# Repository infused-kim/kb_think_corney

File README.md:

# ThinkCorney

A wireless corne / crkbd ergonomic keyboard clone with support for a trackpoint. Built with ergogen v4.

> **Warning**
>
> This keyboard is still under development and not ready for production use.
>
> You can find early stage code on the [develop branch](https://github.com/infused-kim/kb_think_corney/tree/develop) and gerbers in the [repo's releases section](https://github.com/infused-kim/kb_think_corney/releases).
,e
## Credits & Acknowledgements

- [Foostan's corne / crkbd](https://github.com/foostan/crkbd) for making the most popular ergo keyboard that is being used as the basis for this design
- Crehmann's [buzzard](https://github.com/crehmann/Buzzard) and [TPS42](https://github.com/crehmann/TPS42) for pioneering keyboards with trackpoints
- [Jon808517](https://reddit.com/r/ErgoMechKeyboards/comments/11ozztx/choc_spaced_corne_xiao/) for pointing me to the molex pico ezmate connector and joycon batteries
- And of course MrZealot for creating [ergogen](https://github.com/ergogen/ergogen)
- ceoloide for his awesome and creative ergogen tricks in [corney_island](https://github.com/ceoloide/corney-island/)

## License

**TLDR:**

- Personal use with attribution
- Commercial use not allowed

This work is licensed under a
[Creative Commons Attribution-ShareAlike 4.0 International License][cc-by-sa].

[![CC BY-SA 4.0][cc-by-sa-image]][cc-by-sa]

[cc-by-sa]: http://creativecommons.org/licenses/by-sa/4.0/
[cc-by-sa-image]: https://licensebuttons.net/l/by-sa/4.0/88x31.png
[cc-by-sa-shield]: https://img.shields.io/badge/License-CC%20BY--SA%204.0-lightgrey.svg

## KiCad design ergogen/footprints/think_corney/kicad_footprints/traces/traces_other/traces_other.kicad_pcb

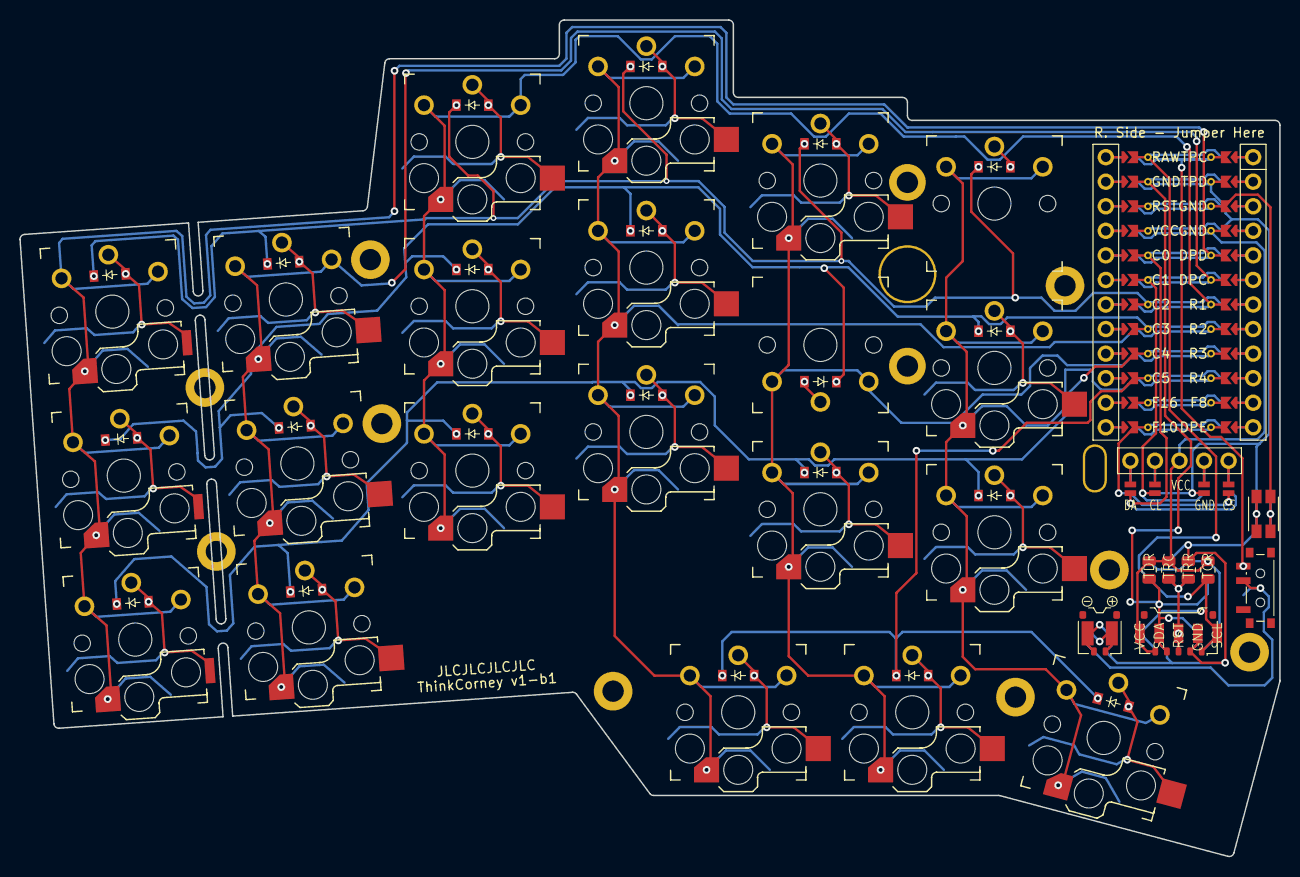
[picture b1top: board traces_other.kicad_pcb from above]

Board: 2 copper layers, 130.3 x 86.5 mm, 112 parts (0 on the bottom side), 46 nets.

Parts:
CONN1: conn_molex_pico_ezmate_1x02
CONN2: conn_molex_pico_ezmate_1x05
D1, D2, D3, D4, D5, D6, D7, D8, D9, D10, D11, D12, D13, D14, D15, D16, D17, D18, D19, D20, D21: ComboDiode
DISP1: nice!view
H1, H2, H3, H4, H5, H6, H7, H8, H9, H10: mounting_hole
ICON1: icon_bat
MCU1: nice_nano
P1", P2", P3", P4", P5", P6", P7", P8", P9", P10", P11", P12", P13", P14", P15", P16", P17", P18", P19", P20", P21", P22", P23", P24", P25", P26", P27", P28", P29", P30", P31", P32", P33", P34", P35", P36", P37", P38", P39", P40", P41", P42", P43", P44", P45", P46", P47", P48", P49": point_debugger
PAD1, PAD2: pads
S1, S2, S3, S4, S5, S6, S7, S8, S9, S10, S11, S12, S13, S14, S15, S16, S17, S18, S19, S20, S21: PG1350
SMD1: smd_805
SW1: power_switch
SW2: sw_reset_side
TP1: trackpoint_mount_t430

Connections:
BAT_P: CONN1.1, PAD1.1, PAD1.2, SW1.2, SW1.5
C0: MCU1.5, S12.1, S13.1, S14.1
C1: MCU1.6, S15.1, S16.1, S17.1
C2: MCU1.7, S1.1, S2.1, S3.1
C3: MCU1.8, S4.1, S5.1, S6.1, S9.1
C4: MCU1.9, S7.1, S10.1, S18.1, S19.1
C5: MCU1.10, S8.1, S11.1, S20.1, S21.1
DISP1_1: DISP1.1, DISP1.14, DISP1.27
DISP1_2: DISP1.2, DISP1.15, DISP1.26
DISP1_4: DISP1.4, DISP1.16, DISP1.25
DISP1_5: DISP1.5, DISP1.17, DISP1.24
DPC: DISP1.11, DISP1.21, MCU1.119
DPD: DISP1.10, DISP1.20, MCU1.120
DPE: DISP1.13, DISP1.23, MCU1.113
GND: CONN1.2, CONN2.2, DISP1.12, DISP1.22, MCU1.2, MCU1.121, MCU1.122, PAD1.1, PAD1.2, PAD2.2, PAD2.4, SMD1.3, SMD1.5, SW2.1
R1: D3.1, D6.1, D9.1, D12.1, D18.1, D20.1, MCU1.118
R2: D2.1, D5.1, D8.1, D11.1, D19.1, D21.1, MCU1.117
R3: D1.1, D4.1, D7.1, D10.1, D13.1, D14.1, MCU1.116
R4: D15.1, D16.1, D17.1, MCU1.115
RAW: MCU1.1, SW1.3, SW1.6
RST: MCU1.3, SW2.2
TPC: CONN2.1, MCU1.124, PAD2.1, PAD2.5, SMD1.2, SMD1.8
TPD: CONN2.4, MCU1.123, PAD2.2, PAD2.4, SMD1.2, SMD1.8
TPR: CONN2.3, PAD2.3, SMD1.4, SMD1.6
VCC: CONN2.5, DISP1.3, MCU1.4, PAD2.1, PAD2.5, SMD1.1, SMD1.3, SMD1.5, SMD1.7
home_cluster: D16.2, S10.2
index_bottom: D13.2, S7.2
index_home: D19.2, S19.2
index_top: D18.2, S18.2
inner_bottom: D14.2, S8.2
inner_cluster: D17.2, S11.2
inner_home: D21.2, S21.2
inner_top: D20.2, S20.2
middle_bottom: D10.2, S4.2
middle_home: D11.2, S5.2
middle_top: D12.2, S6.2
outer_bottom: D1.2, S12.2
outer_cluster: D15.2, S9.2
outer_home: D2.2, S13.2
outer_top: D3.2, S14.2
pinky_bottom: D4.2, S15.2
pinky_home: D5.2, S16.2
pinky_top: D6.2, S17.2
ring_bottom: D7.2, S1.2
ring_home: D8.2, S2.2
ring_top: D9.2, S3.2

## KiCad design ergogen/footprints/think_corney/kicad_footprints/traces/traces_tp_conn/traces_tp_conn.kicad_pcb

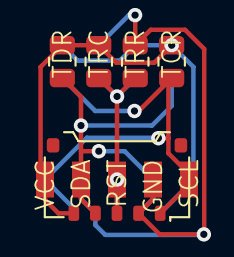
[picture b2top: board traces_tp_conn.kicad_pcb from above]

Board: 2 copper layers, 5 parts (0 on the bottom side), 5 nets.

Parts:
CONN2: conn_molex_pico_ezmate_1x05
P40", P41": point_debugger
PAD2: pads
SMD1: smd_805

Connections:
GND: CONN2.2, PAD2.2, PAD2.4, SMD1.3, SMD1.5
TPC: CONN2.1, PAD2.1, PAD2.5, SMD1.2, SMD1.8
TPD: CONN2.4, PAD2.2, PAD2.4, SMD1.2, SMD1.8
TPR: CONN2.3, PAD2.3, SMD1.4, SMD1.6
VCC: CONN2.5, PAD2.1, PAD2.5, SMD1.1, SMD1.3, SMD1.5, SMD1.7

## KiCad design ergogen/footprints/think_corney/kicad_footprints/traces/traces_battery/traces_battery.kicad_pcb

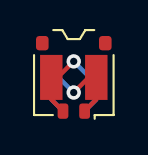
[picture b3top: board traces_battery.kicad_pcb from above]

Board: 2 copper layers, 4 parts (0 on the bottom side), 2 nets.

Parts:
CONN1: conn_molex_pico_ezmate_1x02
P35", P36": point_debugger
PAD1: pads

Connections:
BAT_P: CONN1.1, PAD1.1, PAD1.2
GND: CONN1.2, PAD1.1, PAD1.2

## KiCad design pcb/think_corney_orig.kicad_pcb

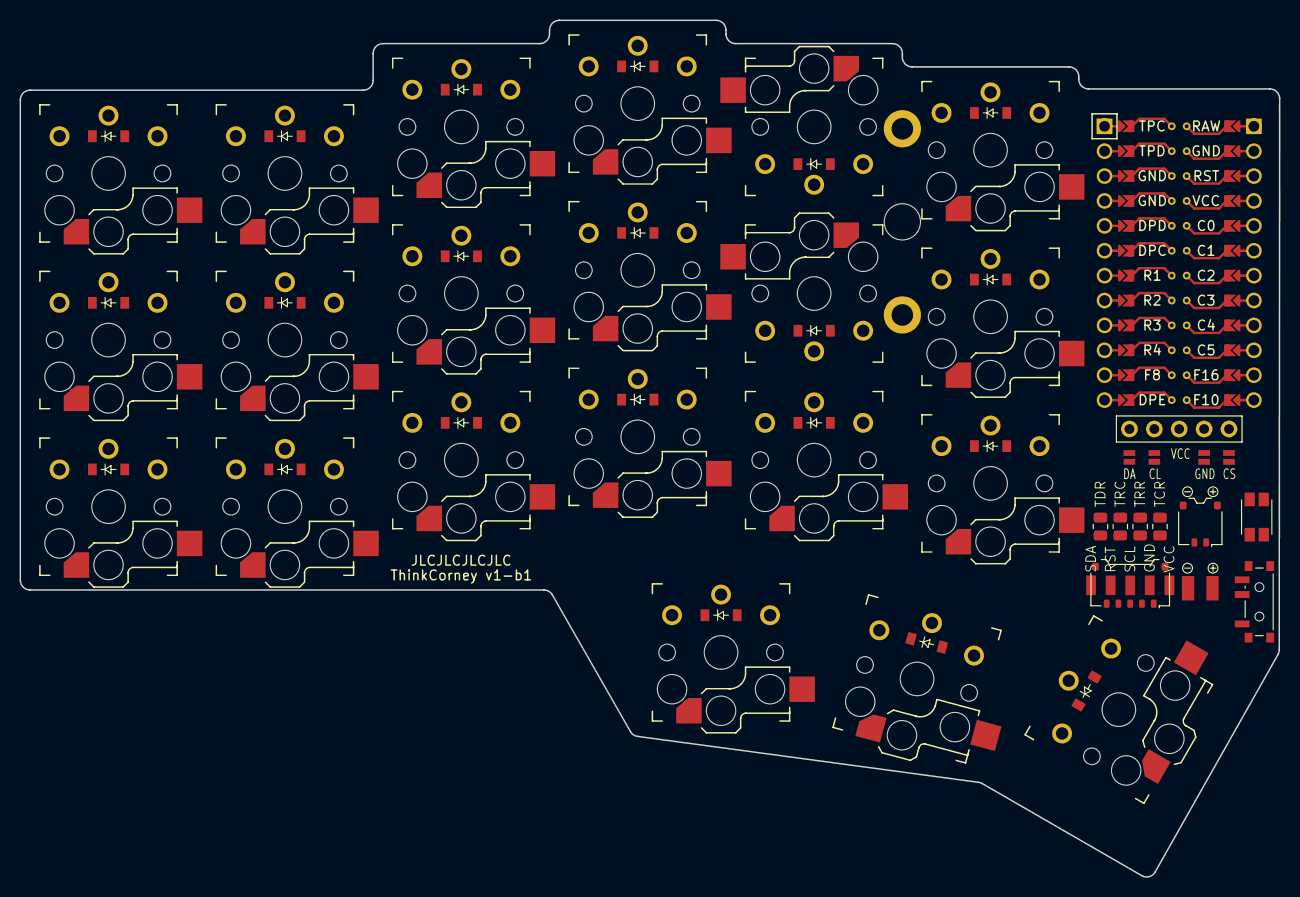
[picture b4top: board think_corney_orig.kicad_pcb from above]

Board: 2 copper layers, 128.5 x 87.4 mm, 54 parts (0 on the bottom side), 46 nets, no tracks yet.

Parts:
CONN1: conn_molex_pico_ezmate_1x02
CONN2: conn_molex_pico_ezmate_1x05
D1, D2, D3, D4, D5, D6, D7, D8, D9, D10, D11, D12, D13, D14, D15, D16, D17, D18, D19, D20, D21: ComboDiode
DISP1: nice!view
ICON1, ICON2: icon_bat
PAD1, PAD2: pads
S1, S2, S3, S4, S5, S6, S7, S8, S9, S10, S11, S12, S13, S14, S15, S16, S17, S18, S19, S20, S21: PG1350
SMD1: smd_805
SW1: power_switch
SW2: sw_reset_side
TP1: trackpoint_mount_t430
_1: ProMicro

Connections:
BAT_P: CONN1.1, PAD1.1, PAD1.2, SW1.2, SW1.5
C0: S1.1, S2.1, S3.1, _1.5
C1: S4.1, S5.1, S6.1, _1.6
C2: S7.1, S8.1, S9.1, _1.7
C3: S10.1, S11.1, S12.1, S17.1, _1.8
C4: S13.1, S18.1, S20.1, S21.1, _1.9
C5: S14.1, S15.1, S16.1, S19.1, _1.10
DISP1_1: DISP1.1, DISP1.14, DISP1.27
DISP1_2: DISP1.2, DISP1.15, DISP1.26
DISP1_4: DISP1.4, DISP1.16, DISP1.25
DISP1_5: DISP1.5, DISP1.17, DISP1.24
DPC: DISP1.11, DISP1.21, _1.19
DPD: DISP1.10, DISP1.20, _1.20
DPE: DISP1.13, DISP1.23, _1.13
GND: CONN1.2, CONN2.2, DISP1.12, DISP1.22, PAD1.1, PAD1.2, PAD2.2, PAD2.4, SMD1.3, SMD1.5, SW2.1, _1.2, _1.21, _1.22
R1: D3.1, D6.1, D9.1, D12.1, D16.1, D21.1, _1.18
R2: D2.1, D5.1, D8.1, D11.1, D15.1, D20.1, _1.17
R3: D1.1, D4.1, D7.1, D10.1, D13.1, D14.1, _1.16
R4: D17.1, D18.1, D19.1, _1.15
RAW: SW1.3, SW1.6, _1.1
RST: SW2.2, _1.3
TPC: CONN2.3, PAD2.3, SMD1.2, SMD1.8, _1.24
TPD: CONN2.5, PAD2.1, PAD2.5, SMD1.2, SMD1.8, _1.23
TPR: CONN2.4, PAD2.2, PAD2.4, SMD1.4, SMD1.6
VCC: CONN2.1, DISP1.3, PAD2.1, PAD2.5, SMD1.1, SMD1.3, SMD1.5, SMD1.7, _1.4
home_cluster: D18.2, S18.2
index_bottom: D13.2, S13.2
index_home: D20.2, S20.2
index_top: D21.2, S21.2
inner_bottom: D14.2, S14.2
inner_cluster: D19.2, S19.2
inner_home: D15.2, S15.2
inner_top: D16.2, S16.2
middle_bottom: D10.2, S10.2
middle_home: D11.2, S11.2
middle_top: D12.2, S12.2
outer_bottom: D1.2, S1.2
outer_cluster: D17.2, S17.2
outer_home: D2.2, S2.2
outer_top: D3.2, S3.2
pinky_bottom: D4.2, S4.2
pinky_home: D5.2, S5.2
pinky_top: D6.2, S6.2
ring_bottom: D7.2, S7.2
ring_home: D8.2, S8.2
ring_top: D9.2, S9.2

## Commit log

2023-04-15 Added initial project structure
2023-04-16 Added initial corne key layout
2023-04-16 Added initial (wrong) corne outline
2023-04-16 Added controller zone
2023-04-16 Added key offset unit
2023-04-16 Added initial pcb design
    Space out PCB section
2023-04-16 PCB: Added reversible promicro_pretty footprint
2023-04-16 Rotate switches to be in the same orientation as most split keyboards
2023-04-17 Added original erogegen v4 choc footprint
2023-04-17 Choc Footprint: Added corner marks to silkmask
2023-04-17 Choc Footprint: Added hotswap outline
2023-04-18 Makefile: Added backups and restoring of traces
2023-04-22 Added ncie!view footprint (not dynamic)
2023-04-22 Added nice!view footprint (not dynamic)
2023-04-22 Nice!View: Added ergogen parameters
2023-04-22 Nice!View: Add show_labels option
2023-04-22 Choc Footprint: Add option to show 1.5u keycap outline
2023-04-22 Choc Keycap FP: Show exact keycap dimensions instead of padded ones
2023-04-22 Ergogen: Show 1.5u outline for last thumb key
2023-04-22 Ergogen: Switch oled to reversible nice!view footprint
2023-04-24 Power Switch FP: Added initial design
2023-04-24 Ergogen: Added power switch
2023-04-24 Bat Conn FP: Added
    Fixed battery connector
2023-04-24 TP Conn FP: Added
2023-04-24 Ergogen: Added battery connector
    Ergogen: Rotated battery connector
2023-04-24 Ergogen: Added trackpoint connector
2023-04-24 Battery Icon FP: Added
2023-04-24 Ergogen: Added battery icon
2023-04-24 Pads FP: Added
2023-04-24 Ergogen: Added pads for battery and trackpoint
2023-04-25 Switch Reset: Added
2023-04-25 Ergogen: Added reset switch
2023-04-25 Pro Micro FP: Added labels
2023-04-25 Ergogen: Added pin labels
2023-04-25 Promicro FP: Set label using net name
2023-04-26 Nice Nano FP: Removed unnecessary usb plug outline parts
2023-04-26 Ergogen: Position display correctly
    Remove old display
2023-04-26 Nice Nano FP: Renamed pro micro to nice!nano
2023-04-26 Nice!View FP: Add display outline and reduce jumper size
2023-04-26 Nice View FP: Add show labels param
2023-04-26 Ergogen: Adjust MCU vertical location based on correct size
2023-04-26 Nice Nano FP: Added nice nano outline on back layer too
2023-04-26 Nice View DP: Display jumpers only when reverse==true
2023-04-26 Ergogen: Assign descriptive nets to pro micro pins
    Fix thumb columns
2023-04-26 Nice View FP: Add option to show jumpers at bottom
2023-04-26 MCU FP: Added nice!nano outline
2023-04-26 Ergogen: Small cleanup
2023-04-26 Ergogen: Switched trackpoint to use high frequency pins
2023-04-27 Text FP: Added
2023-04-27 Ergogen: Added version & jlcpcb order num location
2023-04-27 Power Switch FP: Renamed power_switch -> switch_power
2023-04-27 Ergogen: Fix incorrect thumb keycap size and position
2023-04-27 Choc FP: Make keycap size adjustable and fix incorrect 1.5u size
2023-04-27 Trackpoint Mount FP: Added with T430 outline
2023-04-27 Ergogen: Added trackpoint mount
2023-04-27 Diode FP: Added ergogen original
2023-04-27 Diode FP: Added option to disable throughhole diode
2023-04-28 Choc FP: Added option to show both hotswap and through-hole at once
2023-04-28 Ergogen: Flip trackpoint switches and add non-hotswap soldering option
2023-04-28 Trackpoint Mount FP: Added estimated outline for x240
2023-04-28 Ergogen: Moved TP location one row up
2023-04-28 Ergogen: Show x240 TP outline
2023-04-28 Pads FP: Move labels a little further up
2023-04-28 Ergogen: Move components around
    Ergogen: Move components around
2023-04-28 Ergogen: Remove old reset switch
2023-04-30 SMD 0805 FP: Added
2023-04-30 Pads FP: Fix reverse() changing original nets array
2023-04-30 SMD 0805 FP: Mirror text on back
    Refactor SMD code
2023-04-30 Pads FP: Mirror text on back layer
2023-04-30 Ergogen: Add trackpoint reset circuit
2023-04-30 Makefile: Only copy kicad PCB and not all output files
    If you opened the project in the output fodler, copying everything overwrote the production non-pcb files.
2023-04-30 PCB: Add generated pcb version
2023-04-30 Kicad: Added JLCPCB design rules
2023-04-30 KiCad: Added track widths for regular and power lines
2023-04-30 Choc FP: Made hotswap pads not overlap holes to fix DRC error
2023-04-30 All Footprints: Set footprint type to remove DRC error
    Change virtual to smd attr
2023-04-30 Choc FP: Fix DRC warning “Drilled holes co-located” for hotswap socket
2023-04-30 Choc FP: Fix DRC warning “Drilled holes co-located” for thru hole variant
2023-04-30 Power Switch: FP: Fix DRC warning “Drilled holes co-located”
2023-04-30 Reset Switch FP: Remove silkscreen outline of button to silence DRC warning
2023-04-30 Switch Reset FP: Fix designator and ref
2023-04-30 GIT: Ignore _orig ergogen project files
2023-04-30 KiCad: Fix many DRC problems
2023-05-01 Added test drc violation exclusion
2023-05-04 Nice Nano FP: Added initial rewrite
2023-05-04 Nice Nano FP: Added all dynamic elements and traces
2023-05-05 Ergogen: Switch to new nice!nano footprint
2023-05-05 Nice Nano FP: Remove logs and remove trace nets
2023-05-05 Ergogen: Move controller to top of pcb section
2023-05-05 Makefile: Add build-nt target that doesn’t restore traces
2023-05-05 Ergogen: Move outline section below pcb section
2023-05-05 All FP: Add descriptions
2023-05-05 Text FP: Add text directly to PCB and not through a footprint
2023-05-05 Ergogen: Increase left side outline to fix DRC errors due to cut off pad
2023-05-05 Kicad: Untrack think_corney_orig.kicad_pcb
2023-05-06 Footprints: Moved all footprints to separate repo
2023-05-06 Added basic readme and license
2023-05-06 Makefile: Added install target to update submodules
2023-05-06 README: Add acknowledgements and warning
2023-05-06 Footprints: Updated to latest version
2023-05-06 KiCad: Adjusted DRC warning levels and net defaults
2023-05-06 KiCad: Updated PCB to latest ergogen generated version
2023-05-06 Makefile: Various improvements including locking of traces generated in ergogen
2023-05-07 Ergogen Helper: Moved it to a submodule
2023-07-08 Ergogen: Match mx corney
2023-07-08 Ergogen: Switch back to choc config
2023-07-08 Ergogen: Added preset function
    Based on the work of @ ceoloide in
    https://github.com/ceoloide/corney-island/tree/main
2023-07-09 Ergogen: Added chocofi profile
2023-07-09 Ergogen: Added kim profile initial
2023-07-09 Ergogen: Add ability to use 1u or 1.5u inner thumb key
2023-07-09 Ergogen: Remove units section from presets
2023-07-09 Ergogen: Reduce corner radius of board outline
2023-07-10 Ergogen: Added splay and adjusted stagger for Kim preset
2023-07-15 Ergogen: Make thumb outline dynamic
2023-07-16 Ergogen: Removed direct use of cfg_ units
2023-07-16 Ignore debug directory
2023-07-16 Ergogen: Added cutout for battery wires
2023-07-16 Ergogen: Added point debugger
2023-07-16 Ergogen: Added meta section
2023-07-18 Ergogen: Added mounting holes
2023-07-18 Ergogen: Adjust intersect to new parameters
2023-07-18 Ergogen: Updated mounting holes for new to support oval hole parameters
2023-07-18 Ergogen: Added oval hole to put battery connector through
2023-07-18 Ergogen: Removed battery wire cutout on the right side
2023-07-18 Ergogen: Added display cover holes
2023-07-18 Ergogen: Move components around display cover holes
2023-07-18 Ergogen: Change trackpoint connector pin order to red trackpoint
2023-07-19 Footprints: Use nice!nano fp that has more space for traces
2023-07-19 PCB: Update to latest pcb version with initial traces
2023-07-19 Git: Ignore svg files in pcb dir
2023-07-19 Ergogen: Added breakoff column cutouts
2023-07-19 Ergogen: Switched to trackpoints T460s outline
2023-07-19 Ergogen: Allow presets to unflip keys
    Ergogen: Move diode up for flipped keys
2023-08-01 Ergogen: Added initial key traces
2023-08-01 Ergogen: Improved key traces
2023-08-01 Footprints: Updated to latest version of lib
2023-08-01 Ergogen: Adjusted diode routing
2023-08-06 Ergogen: Reduce size of key hotswap pads to silence edge DRC warnings
2023-08-26 Ergogen: Updated to new nice nano footprint
2023-08-26 Footprints: Added traces_key footprint kicad file
    Ignore kicad_pro for traces kicad files
2023-08-26 Key Traces: Fix too long traces when using smaller hotswap pads
2023-08-27 Traces: Added initial matrix traces
2023-08-27 Ergogen: Made matrix traces selectable based on profile
2023-08-27 Makefile: Add target to run in debug mode
2023-08-27 Ergogen: Reduce repetition in key footprint definition
2023-08-27 Ergogen: Added ability to customize keys around TP mount individually
2023-08-27 Ergogen: Adjust TP keys for kim and choc_corne
2023-08-28 Ergogen: Added traces for keys without hotswap
2023-08-28 Footprints: Moved traces pcb files to subfolders
2023-08-28 Traces: Fixed matrix traces for TP key changes
    Added pcb
2023-08-28 Makefile: Add target to restore kikad proj file
2023-08-28 Traces: Added traces for batter conn + pad
2023-08-28 Traces: Added trackpoint conn traces
2023-08-28 Traces: Added display traces
2023-08-28 Traces: Added other traces
2023-08-28 Traces: Added remaining missing traces
2023-08-28 Traces: Fix potential DRC clearance errors in battery footprint
2023-08-28 Traces: Fix potential DRC clearance errors in TP conn footprint
2023-08-28 Makefile: Added gerber target
2023-08-28 PCB: Submitted test to jlcpcb
2023-08-29 Ergogen: Decreased mounting hole sizes to 2.2mm
2023-08-29 Ergogen: Increase battery hole size
2023-08-29 Ergogen: Moved reset switch closer to board edge
2023-08-29 Repo: Add gerbers readme
2023-08-29 Repo: Deleted unneeded files and directories
2023-08-29 Repo: Added a readme
